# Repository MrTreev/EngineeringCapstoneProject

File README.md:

# EngineeringCapstoneProject

RMIT Engineering Capstone Project 2022

An investigation into materials and components for use in wearable technologies and the development of a holistic health monitoring system

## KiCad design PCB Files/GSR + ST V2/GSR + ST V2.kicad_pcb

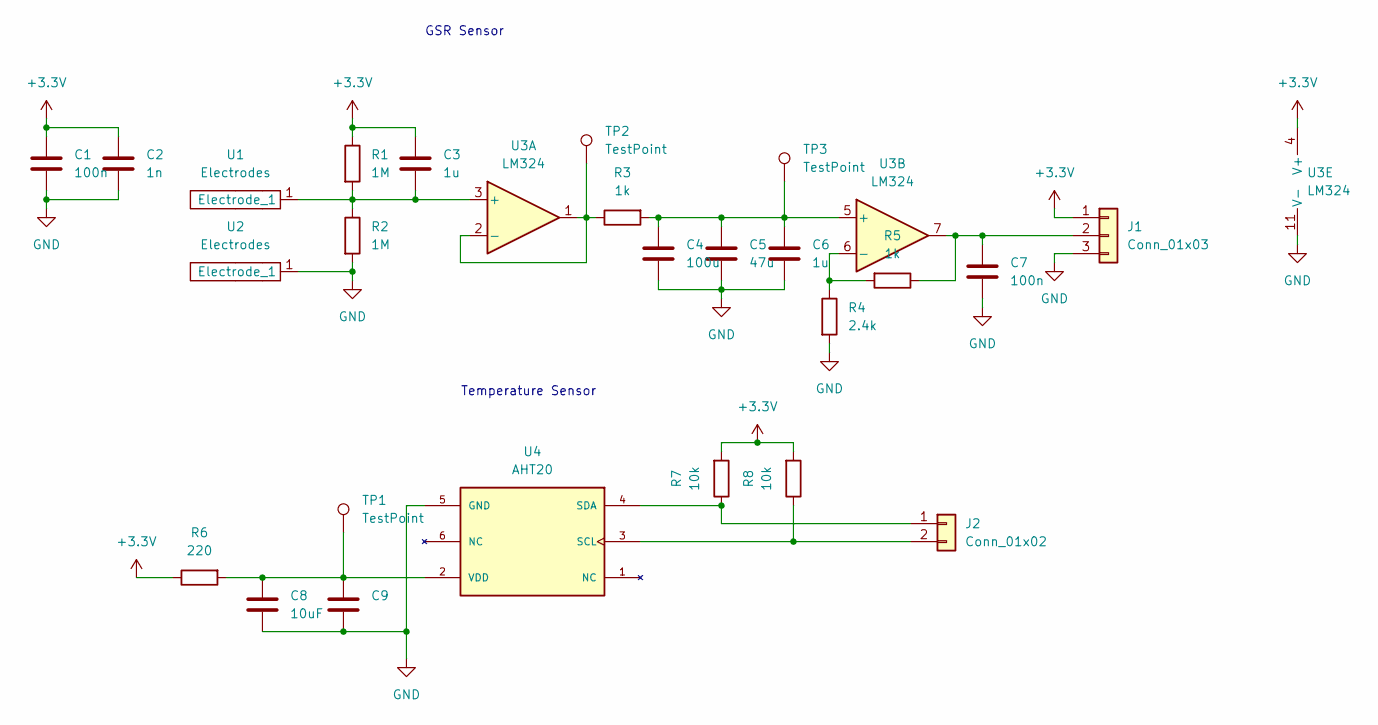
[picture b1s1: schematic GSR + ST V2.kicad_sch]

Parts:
C1, C7: 100n; C_1206_3216Metric
C2: 1n; C_1206_3216Metric
C3, C6: 1u; C_1206_3216Metric
C4: 100u; C_1206_3216Metric
C5: 47u; C_1206_3216Metric
C8: 10uF; C_1206_3216Metric
C9: C_1206_3216Metric
J1: Conn_01x03; PinHeader_1x03_P2.54mm_Vertical
J2: Conn_01x02; PinHeader_1x02_P2.54mm_Vertical
R1, R2: 1M; R_1206_3216Metric_Pad1.30x1.75mm_HandSolder
R3, R5: 1k; R_1206_3216Metric_Pad1.30x1.75mm_HandSolder
R4: 2.4k; R_1206_3216Metric_Pad1.30x1.75mm_HandSolder
R6: 220; R_1206_3216Metric_Pad1.30x1.75mm_HandSolder
R7, R8: 10k; R_1206_3216Metric_Pad1.30x1.75mm_HandSolder
TP1, TP2, TP3: TestPoint; TestPoint_Pad_D1.0mm
U1, U2: Electrodes; Electrode
U3: LM324; SOIC-14_3.9x8.7mm_P1.27mm
U4: AHT20; PSON100P300X300X110-6N; PARTREV V1.0

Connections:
+3V3: C1.1, C2.1, C3.1, J1.1, R1.1, R6.1, R7.2, R8.2, U3.4 (V+)
GND: C1.2, C2.2, C4.2, C5.2, C6.2, C7.2, C8.2, C9.2, J1.3, R2.2, R4.2, U2.1 (Electrode_1), U3.11 (V-), U4.5 (GND)
unnamed: C3.2, R1.2, R2.1, U1.1 (Electrode_1), U3.3 (+)
unnamed: C4.1, C5.1, C6.1, R3.2, TP3.1, U3.5 (+)
unnamed: C7.1, J1.2, R5.1, U3.7
unnamed: C8.1, C9.1, R6.2, TP1.1, U4.2 (VDD)
unnamed: J2.1, R7.1, U4.4 (SDA)
unnamed: J2.2, R8.1, U4.3 (SCL)
unnamed: R3.1, TP2.1, U3.1, U3.2 (-)
unnamed: R4.1, R5.2, U3.6 (-)

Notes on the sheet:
Temperature Sensor
GSR Sensor

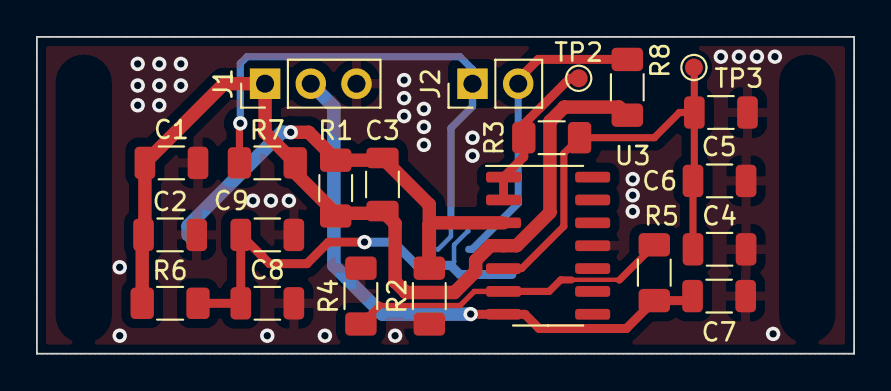
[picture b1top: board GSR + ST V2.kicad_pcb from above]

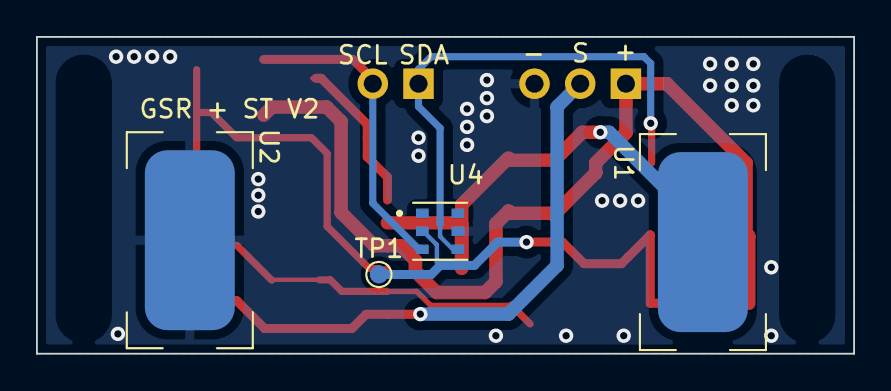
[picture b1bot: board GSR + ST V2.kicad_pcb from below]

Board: 2 copper layers, 45.4 x 17.6 mm, 26 parts (4 on the bottom side), 10 nets.

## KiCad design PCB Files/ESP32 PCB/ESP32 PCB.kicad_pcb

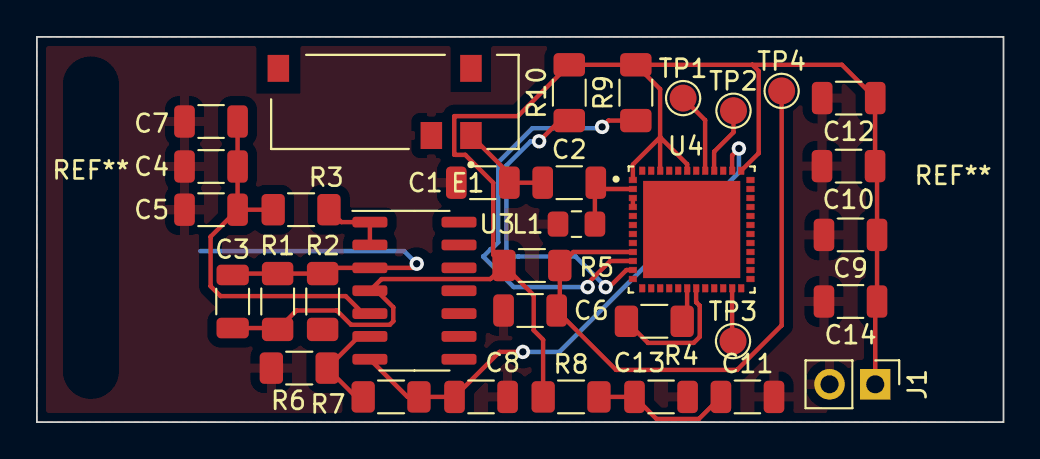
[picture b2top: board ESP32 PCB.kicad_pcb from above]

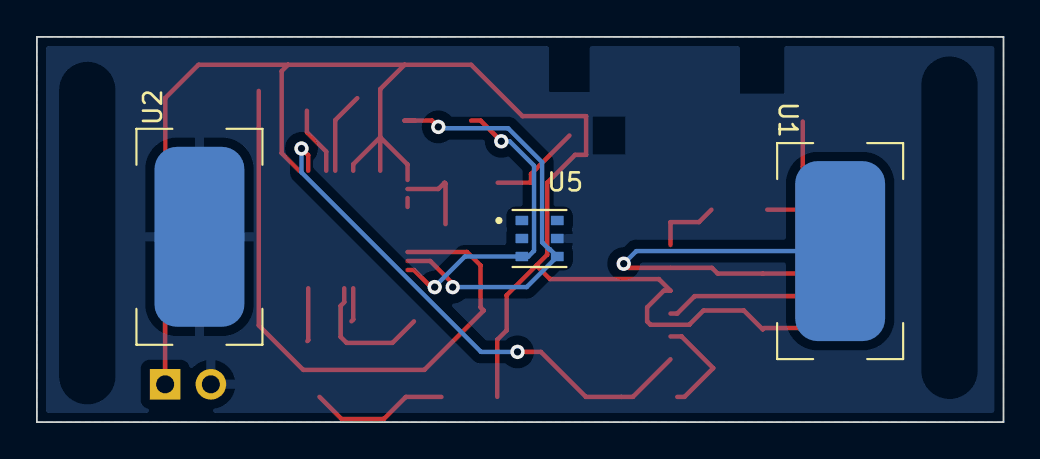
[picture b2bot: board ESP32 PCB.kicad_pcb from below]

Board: 2 copper layers, 53.7 x 21.4 mm, 36 parts (3 on the bottom side), 17 nets.

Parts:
C1: 2.7pF; C_1206_3216Metric
C2: 4.7pF; C_1206_3216Metric
C3, C7: 1u; C_1206_3216Metric
C4: 100u; C_1206_3216Metric
C5: 47u; C_1206_3216Metric
C6, C10, C13: 0.1uF; C_1206_3216Metric
C8, C12: 100n; C_1206_3216Metric
C9, C11: 10uF; C_1206_3216Metric
C14: 1n; C_1206_3216Metric
E1: PRO-OB-440; ANT_PRO-OB-440
J1: Conn_01x02; PinHeader_1x02_P2.54mm_Vertical
L1: 1.6nH; L_0805_2012Metric_Pad1.15x1.40mm_HandSolder
R1, R2: 1M; R_1206_3216Metric_Pad1.30x1.75mm_HandSolder
R3, R7: 1k; R_1206_3216Metric_Pad1.30x1.75mm_HandSolder
R4, R5: 10K; R_1206_3216Metric_Pad1.30x1.75mm_HandSolder
R6: 2.4k; R_1206_3216Metric_Pad1.30x1.75mm_HandSolder
R8: 220; R_1206_3216Metric_Pad1.30x1.75mm_HandSolder
R9, R10: 10k; R_1206_3216Metric_Pad1.30x1.75mm_HandSolder
TP1, TP2, TP3, TP4: TestPoint; TestPoint_Pad_D1.5mm
U1, U2: Electrodes; Electrode
U3: LM324; SOIC-14_3.9x8.7mm_P1.27mm
U4: ESP32-PICO-D4; PQFN50P700X700X104-49N
U5: AHT20; PSON100P300X300X110-6N

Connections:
+3V3: C3.1, C9.1, C10.1, C12.1, C14.1, J1.1, R1.1, R4.1, R5.1, R8.1, R9.2, R10.2, U3.4 (V+), U4.1 (VDDA), U4.3 (VDDA3P3), U4.4 (VDDA3P3), U4.19 (VDD3P3_RTC), U4.37 (VDD3P3_CPU), U4.43 (VDDA), U4.46 (VDDA)
GND: C1.1, C4.2, C5.2, C6.2, C7.2, C8.2, C9.2, C10.2, C11.2, C12.2, C13.2, C14.2, E1.2, J1.2, L1.1, R2.2, R6.2, U2.1 (Electrode_1), U3.11 (V-), U4.49 (GND), U5.5 (GND)
unnamed: C1.2, C2.1, E1.1
unnamed: C2.2, L1.2, U4.2 (LNA_IN)
unnamed: C3.2, R1.2, R2.1, U1.1 (Electrode_1), U3.3 (+)
unnamed: C4.1, C5.1, C7.1, R3.2, U3.5 (+)
unnamed: C6.1, R5.2, TP4.1, U4.9 (EN)
unnamed: C11.1, C13.1, R8.2, U5.2 (VDD)
unnamed: R3.1, U3.1, U3.2 (-)
unnamed: R6.1, R7.2, U3.6 (-)
unnamed: TP1.1, U4.41 (U0TXD)
unnamed: TP2.1, U4.40 (U0RXD)
unnamed: TP3.1, U4.23 (IO0)
unnamed: R4.2, U4.18 (IO12)
S: C8.1, R7.1, U3.7, U4.38 (IO19)
SCL: R10.1, U4.11 (IO35), U5.3 (SCL)
SDA: R9.1, U4.10 (IO34), U5.4 (SDA)

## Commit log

2022-03-09 Initaial Repo Initialisation
2022-03-10 init
2022-03-10 Added sections to proposal rmd
2022-03-11 Changed date and added course code
2022-03-14 added articles, generated references, and started a contribution table
2022-03-16 added more papers and recompiled document
2022-03-17 changed project, removed papers
2022-03-18 Added working title to readme
2022-03-24 collected papers
2022-03-25 para1
2022-03-26 added sweat sensor papers and references
2022-03-28 IDT and Sweat rate
2022-03-28 added others work
2022-03-28 added images
2022-03-28 added name
2022-03-28 added project risks table
2022-03-28 finish up proposal except one alteration
2022-03-30 during changes
2022-03-30 after revision section
2022-04-01 Minor fixes
2022-04-02 all before risk table
2022-04-02 added risk assessment and combined to full document
2022-04-03 Final copy
2022-04-08 test
2022-04-13 updated FullReport to not canvas res
2022-04-27 Part Selection
2022-05-04 added testing folder
2022-05-04 TestingCode
2022-05-04 read adc and send via ble
2022-05-10 New folder
2022-05-10 Commenting code
2022-05-11 altered files
2022-05-12 Test RMD upload
2022-05-12 Testing WIP
2022-05-12 Cleaned and compiled report
2022-05-17 Added data visualization files
2022-05-19 continued testing
2022-05-21 testing works
2022-05-22 added extra graphs and sensor readers
2022-05-22 TestingModified
2022-05-23 Save Images as File
2022-05-23 Un doxxing myself
2022-05-24 Merge
2022-05-25 Final Working Version
2022-05-25 images
2022-05-26 More Reports
2022-05-26 Did a bit of changes
2022-05-26 Push Main PDF
2022-05-27 Contribution Table
2022-05-28 retrieved unadulterated report before git changed stuff and fixed a bunch more referencing
2022-05-28 retrieved unadulterated report before git changes stuff again and fixed a bunch more referencing
2022-05-28 Finalised Report without image size changes
2022-05-28 Finalised Typeset report
2022-05-30 Demo Prep
2022-05-30 Changed Timelines
2022-07-07 Added Papers to folder and sorted stuff, more to come
2022-08-01 Upload PCB Files
2022-08-03 Completion Plan Ported and images added for Final report
2022-08-03 Location testing changes to code
2022-08-03 Removed Random md File
2022-08-06 near-final report draft
2022-08-07 updated images
2022-08-07 Final Pass
2022-09-10 added db test file
2022-09-10 FIle Add
2022-09-10 Subs code
2022-09-10 User
2022-09-12 SW Filtering
2022-09-26 Cleaning up git
2022-09-26 Cleaning and setting up for MATLAB
2022-09-26 Added Sensor Data File
2022-10-16 Finalised Report
